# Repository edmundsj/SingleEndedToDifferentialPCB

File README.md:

# Single-Ended to Differential Converter PCB
Single-ended to differential Printed Circuit Board (PCB) for converting a single-ended signal into a differential one.

## Specifications
- Single SMA analog input
- Supply voltage 2.2V to 5V
- Single XLR analog output
- ~200nV/rtHz input-referred voltage noise

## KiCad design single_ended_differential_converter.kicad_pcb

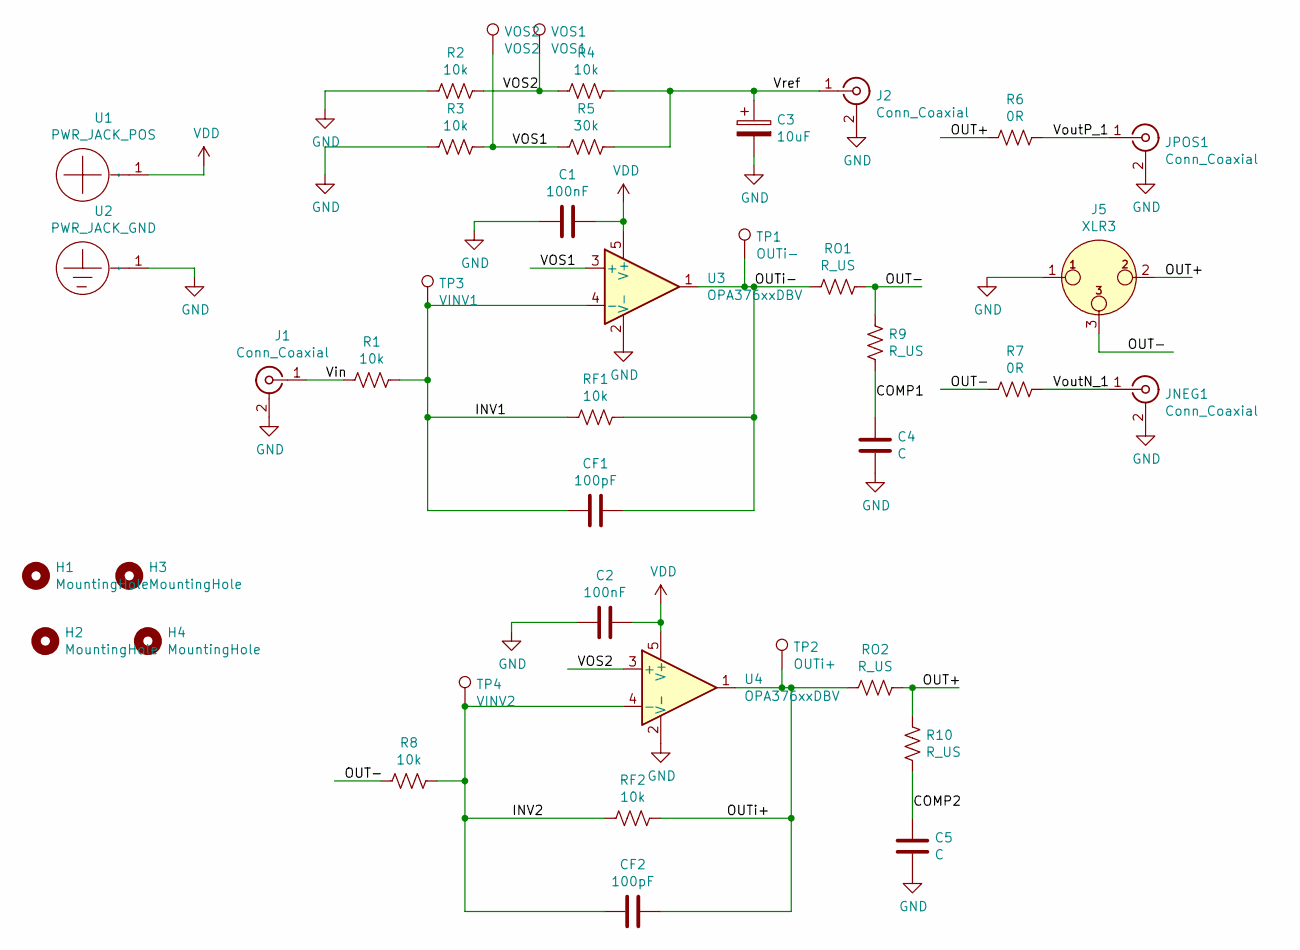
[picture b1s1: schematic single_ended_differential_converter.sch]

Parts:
C1, C2: 100nF; C_0805_2012Metric_Pad1.15x1.40mm_HandSolder
C3: 10uF; C_0805_2012Metric_Pad1.15x1.40mm_HandSolder
C4, C5: C; C_0805_2012Metric_Pad1.15x1.40mm_HandSolder
CF1, CF2: 100pF; C_0805_2012Metric_Pad1.15x1.40mm_HandSolder
H1, H2, H3, H4: MountingHole; m3_mounting_hole
J1, J2: Conn_Coaxial; CON-SMA-EDGE-S
J5: XLR3; Jack_XLR_Switchcraft
JNEG1: Conn_Coaxial; CON-SMA-EDGE-S
JPOS1: Conn_Coaxial; CON-SMA-EDGE-S
R1, R2, R3, R4, R8: 10k; R_0805_2012Metric_Pad1.15x1.40mm_HandSolder
R5: 30k; R_0805_2012Metric_Pad1.15x1.40mm_HandSolder
R6, R7: 0R; R_0805_2012Metric_Pad1.15x1.40mm_HandSolder
R9, R10: R_US; R_0805_2012Metric_Pad1.15x1.40mm_HandSolder
RF1, RF2: 10k; R_0805_2012Metric_Pad1.15x1.40mm_HandSolder
RO1, RO2: R_US; R_0805_2012Metric_Pad1.15x1.40mm_HandSolder
TP1: OUTi-; TestPoint_Keystone_5000-5004_Miniature
TP2: OUTi+; TestPoint_Keystone_5000-5004_Miniature
TP3: VINV1; TestPoint_Keystone_5000-5004_Miniature
TP4: VINV2; TestPoint_Keystone_5000-5004_Miniature
U1: PWR_JACK_POS; Banana_Jack_1Pin
U2: PWR_JACK_GND; Banana_Jack_1Pin
U3, U4: OPA376xxDBV; SOT-23-5
VOS1: VOS1; TestPoint_Keystone_5000-5004_Miniature
VOS2: VOS2; TestPoint_Keystone_5000-5004_Miniature

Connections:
/COMP1: C4.1, R9.2
/COMP2: C5.1, R10.2
/INV1: CF1.2, R1.1, RF1.2, TP3.1, U3.4 (-)
/INV2: CF2.2, R8.1, RF2.2, TP4.1, U4.4 (-)
/OUT+: J5.2, R6.2, R10.1, RO2.1
/OUT-: J5.3, R7.2, R8.2, R9.1, RO1.1
/OUTi+: CF2.1, RF2.1, RO2.2, TP2.1, U4.1
/OUTi-: CF1.1, RF1.1, RO1.2, TP1.1, U3.1
/VOS1: R3.1, R5.2, U3.3 (+), VOS2.1
/VOS2: R2.1, R4.2, U4.3 (+), VOS1.1
/Vin: J1.1 (In), R1.2
/VoutN_1: JNEG1.1 (In), R7.1
/VoutP_1: JPOS1.1 (In), R6.1
/Vref: C3.1, J2.1 (In), R4.1, R5.1
GND: C1.2, C2.2, C3.2, C4.2, C5.2, J1.2 (Ext), J2.2 (Ext), J5.1, JNEG1.2 (Ext), JPOS1.2 (Ext), R2.2, R3.2, U2.1, U3.2 (V-), U4.2 (V-)
VDD: C1.1, C2.1, U1.1, U3.5 (V+), U4.5 (V+)

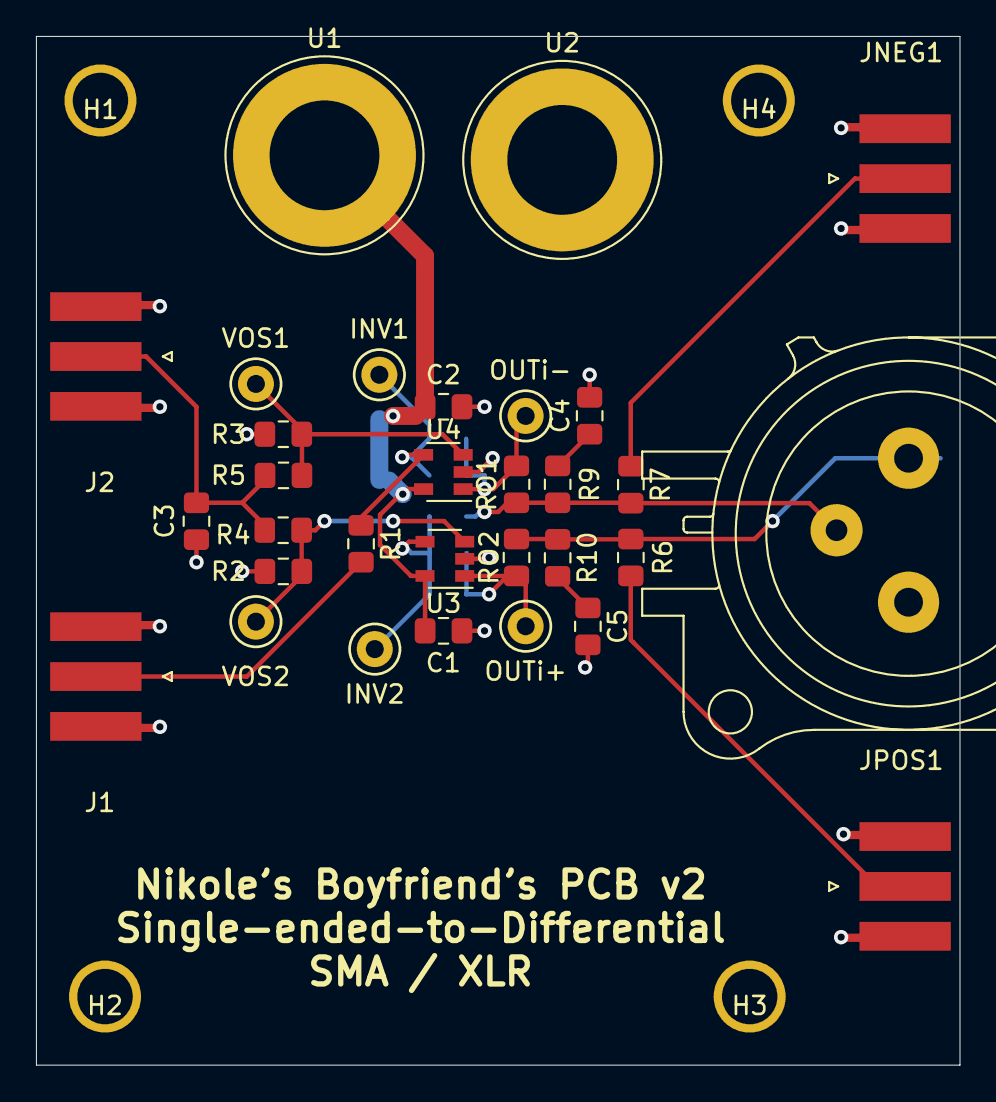
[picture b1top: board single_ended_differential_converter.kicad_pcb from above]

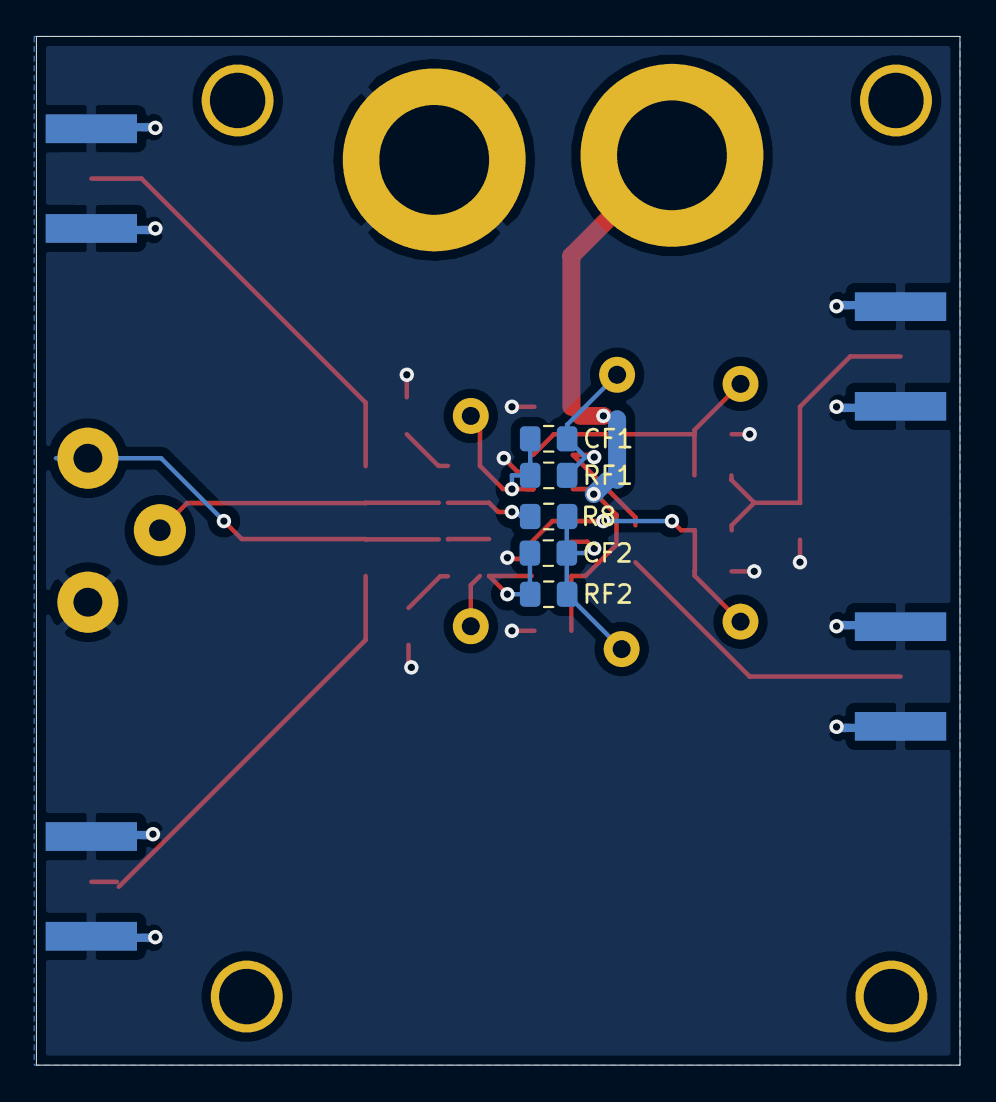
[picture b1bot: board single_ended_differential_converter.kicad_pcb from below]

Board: 2 copper layers, 51.3 x 57.2 mm, 40 parts (5 on the bottom side), 16 nets.

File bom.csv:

"Id";"Designator";"Package";"Quantity";"Designation";"Supplier and ref";
1;"J5";"Jack_XLR_Switchcraft";1;"XLR3";;;
2;"C3";"C_0805_2012Metric_Pad1.15x1.40mm_HandSolder";1;"10uF";;;
3;"TP4";"TestPoint_Keystone_5000-5004_Miniature";1;"INV2";;;
4;"TP3";"TestPoint_Keystone_5000-5004_Miniature";1;"INV1";;;
5;"TP2";"TestPoint_Keystone_5000-5004_Miniature";1;"OUTi+";;;
6;"TP1";"TestPoint_Keystone_5000-5004_Miniature";1;"OUTi-";;;
7;"U2";"Banana_Jack_1Pin";1;"PWR_JACK_GND";;;
8;"U4,U3";"SOT-23-5";2;"OPA376xxDBV";;;
9;"RO2,RO1,R10,R9";"R_0805_2012Metric_Pad1.15x1.40mm_HandSolder";4;"R_US";;;
10;"RF2,R8,RF1,R4,R3,R2,R1";"R_0805_2012Metric_Pad1.15x1.40mm_HandSolder";7;"10k";;;
11;"CF2,CF1";"C_0805_2012Metric_Pad1.15x1.40mm_HandSolder";2;"100pF";;;
12;"C5,C4";"C_0805_2012Metric_Pad1.15x1.40mm_HandSolder";2;"C";;;
13;"C2,C1";"C_0805_2012Metric_Pad1.15x1.40mm_HandSolder";2;"100nF";;;
14;"H4,H3,H2,H1";"m3_mounting_hole";4;"MountingHole";;;
15;"R7,R6";"R_0805_2012Metric_Pad1.15x1.40mm_HandSolder";2;"0R";;;
16;"VOS2";"TestPoint_Keystone_5000-5004_Miniature";1;"VOS2";;;
17;"VOS1";"TestPoint_Keystone_5000-5004_Miniature";1;"VOS1";;;
18;"U1";"Banana_Jack_1Pin";1;"PWR_JACK_POS";;;
19;"R5";"R_0805_2012Metric_Pad1.15x1.40mm_HandSolder";1;"30k";;;
20;"JPOS1,JNEG1,J2,J1";"CON-SMA-EDGE-S";4;"Conn_Coaxial";;;

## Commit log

2020-10-05 adding version 1.1 (initial fabricated version with wrong-facing connector and low load capacitance drive converter
2020-10-05 added files for version 2
2020-10-05 added updated gerbers for version 2
2020-10-06 updated readme with basic description / specifications
2020-10-06 added kicad-generated BOM
2020-10-10 added gitignore for cache
2021-01-19 updated PCB
